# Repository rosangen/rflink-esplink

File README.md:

RFLink-ESPLink pcb
===================

This is a PCB card for use with [RFLink](http://rflink.nl/blog2/) software, [ESP-Link](https://github.com/jeelabs/esp-link), [ESP-Easy](https://github.com/letscontrolit/ESPEasy) or what you find fits you best.
It is mainly for my purpose of getting [IKEA anslut remote control](http://www.ikea.com/se/sv/catalog/products/90300773/) in my Home Assistant setup. And for measure my pellets and power meter.

**You can fill the board so it meat yours need!!**

Use it as a RFLink with receiver and transmitter, and connect to server with USB, add CC2500 module for IKEA asnlut support.

Add a Wemos D1 Mini to get the RFLink more portable and communicate via WiFi via [tcp-mode](https://home-assistant.io/components/rflink/#tcp-mode).
If you just are interested in IKEA anslut, use a CC2500 module + Arduino Pro Mini + Wemos D1 Mini and communicate with MQTT.
 
Inspired by https://github.com/NDBCK/Ansluta-Remote-Controller for Arduino Pro Mini support, and also https://github.com/Genestealer/Home-Assistant-RFLink-Gateway-ESP8266 fore the komplete setup!

Schema
-----------

[Schema pdf](https://github.com/rosangen/rflink-esplink/blob/master/PCB/RfLink-ESPlink.pdf?raw=true "RfLink-ESPlink.pdf")

PCB
------
Size 94 x 96mm

Fore the moment, no PCB is tested, more info to come!

Configurations
-----------
Some configurations explained:

### RFLink USB connected:
```
IC2 Arduino Mega, IC5 Transmitter, IC6 or IC7 Receiver, X1 Antenna connection. 
Option 1: C5,C6 and C7 for better reception with RXB6 receiver.
Option 2: R3, R9, LED1 so se TX communication is visible (receiving data).
```

### RFLink with ESP-link:
```
IC1 ESP, IC2 Arduino Mega, IC5 Transmitter, IC6 or IC7 Receiver. R1, R2, R3.
- Ansluta option: IC4 CC2500, R4-7, C8.
- Option 1 and 2, se above.
```

### Anluta MQTT:
```
IC1 ESP, IC3 Arduino Pro Mini 3.3v, IC4 CC2500 modul, C8.
- Option R9 LED1
```

### EasyESP:
With 1-wire temp and power meter sensor.
```
IC1 ESP, R20-R25 if needed. If lead needed: R10, R11, LED 2, LED3, R20, JP1, R21, JP2. 
Temperatur: DS18B20 connected to JP1
Power meter: LTR4206E ir detector connected to JP2.
```

### Onboard 3.3v converter
If you don't want to use Mega 2560 or ESP interna 3.3v converter you can add U1 (AMS1117 3.3v) and C2, C3, C4.
- PS1 Power selector is for choose input source, IC2 Mega or IC1 ESP 5 volt. (JP5 can only be in used if not Mega 2560 is in use).
- PS2 is the 3.3v source selector, use INT with interna 3.3v converter.

Komponents
-----------

<table>
<tbody>
<tr>
<td><strong>Part</strong></td>
<td><strong>Value</strong></td>
<td><strong>Device/Type</strong></td>
<td><strong>Package/Info</strong></td>
</tr>
<tr>
<td>C1</td>
<td>10&micro;F</td>
<td>CAPACITOR</td>
<td>E2-5</td>
</tr>
<tr>
<td>C2</td>
<td>100nF</td>
<td>CAPACITOR</td>
<td>C0805</td>
</tr>
<tr>
<td>C3</td>
<td>0.1&micro;F</td>
<td>CAPACITOR</td>
<td>E2-5</td>
</tr>
<tr>
<td>C4</td>
<td>10&micro;F</td>
<td>CAPACITOR</td>
<td>E2-5</td>
</tr>
<tr>
<td>C5</td>
<td>100nF</td>
<td>CAPACITOR</td>
<td>C0805</td>
</tr>
<tr>
<td>C6</td>
<td>100nF</td>
<td>CAPACITOR</td>
<td>C0805</td>
</tr>
<tr>
<td>C7</td>
<td>10&micro;F</td>
<td>CPOL-EUE2-5</td>
<td>E2-5</td>
</tr>
<tr>
<td>C8</td>
<td>100nF</td>
<td>CAPACITOR</td>
<td>C0805</td>
</tr>
<tr>
<td>C9</td>
<td>10&micro;F</td>
<td>CPOL-EUE2-5</td>
<td>E2-5</td>
</tr>
<tr>
<td>IC1</td>
<td>WEMOS D1 MINI</td>
<td>WEMOS D1 MINI</td>
<td>&nbsp;WeMos.cc</td>
</tr>
<tr>
<td>IC2</td>
<td>ARDUINO-MEGA</td>
<td>ARDUINO MEGA 2560</td>
</tr>
<tr>
<td>IC3</td>
<td>PRO MINI 3.3V</td>
<td>ARDUINO PRO MINI</td>
</tr>
<tr>
<td>IC4</td>
<td>CC2500</td>
<td>CC2500 MODULE</td>
</tr>
<tr>
<td>IC5</td>
<td>TRANSMITTER 433MHZ</td>
<td>TRANSMITTER 433MHZ</td>
</tr>
<tr>
<td>IC6</td>
<td>RXB6</td>
<td>RECEIVER</td>
</tr>
<tr>
<td>IC7</td>
<td>RTX-MID</td>
<td>RTX-MID</td>
<td>Aurel</td>
</tr>
<tr>
<td>IC8</td>
<td>NRF24L01A</td>
<td>NRF24L01A</td>
<td>NRF24L01</td>
</tr>
<tr>
<td>IC9</td>
<td>ESP-01</td>
<td>ESP8266 Wifi module 01</td>
</tr>
<tr>
<td>J1</td>
<td>JUMPER 2 SMD</td>
<td>Jumper</td>
<td>Aktivate CC2500</td>
</tr>
<tr>
<td>J2</td>
<td>JUMPER 3 SMD</td>
<td>Jumper</td>
<td>3.3 or 5.0V Aurel</td>
</tr>
<tr>
<td>JP1</td>
<td>GS015S-3.81-3P</td>
<td>PCB terminal block</td>
<td>PCB terminal block</td>
</tr>
<tr>
<td>JP2</td>
<td>GS015S-3.81-3P</td>
<td>PCB terminal block</td>
<td>PCB terminal block</td>
</tr>
<tr>
<td>JP3</td>
<td>GS015S-3.81-3P</td>
<td>PCB terminal block</td>
<td>PCB terminal block</td>
</tr>
<tr>
<td>JP4</td>
<td>GS015S-3.81-2P</td>
<td>PCB terminal block</td>
<td>PCB terminal block</td>
</tr>
<tr>
<td>JP5</td>
<td>GS015S-3.81-2P</td>
<td>PCB terminal block</td>
<td>PCB terminal block</td>
</tr>
<tr>
<td>LED1</td>
<td>LED1206</td>
<td>LED-1206</td>
<td>LEDs</td>
</tr>
<tr>
<td>LED2</td>
<td>LED1206</td>
<td>LED-1206</td>
<td>LEDs</td>
</tr>
<tr>
<td>LED3</td>
<td>LED1206</td>
<td>LED-1206</td>
<td>LEDs</td>
</tr>
<tr>
<td>LED4</td>
<td>LED1206</td>
<td>LED-1206</td>
<td>LEDs</td>
</tr>
<tr>
<td>PS1</td>
<td>JUMPER</td>
<td>2 TO 1 POWER</td>
</tr>
<tr>
<td>PS2</td>
<td>JUMPER</td>
<td>3 TO 1 POWER</td>
</tr>
<tr>
<td>R1</td>
<td>470R</td>
<td>RESISTOR R0805</td>
<td>R0805</td>
</tr>
<tr>
<td>R2</td>
<td>470R</td>
<td>RESISTORR0805</td>
<td>R0805</td>
</tr>
<tr>
<td>R3</td>
<td>470R</td>
<td>RESISTORR0805</td>
<td>R0805</td>
</tr>
<tr>
<td>R4</td>
<td>470R</td>
<td>RESISTORR0805</td>
<td>R0805</td>
</tr>
<tr>
<td>R5</td>
<td>470R</td>
<td>RESISTORR0805</td>
<td>R0805</td>
</tr>
<tr>
<td>R6</td>
<td>470R</td>
<td>RESISTORR0805</td>
<td>R0805</td>
</tr>
<tr>
<td>R7</td>
<td>470R</td>
<td>RESISTORR0805</td>
<td>R0805</td>
</tr>
<tr>
<td>R8</td>
<td>1K</td>
<td>RESISTORR0805</td>
<td>R0805</td>
</tr>
<tr>
<td>R9</td>
<td>1K</td>
<td>RESISTORR0805</td>
<td>R0805</td>
</tr>
<tr>
<td>R10</td>
<td>1K</td>
<td>RESISTORR0805</td>
<td>R0805</td>
</tr>
<tr>
<td>R11</td>
<td>1K</td>
<td>RESISTORR0805</td>
<td>R0805</td>
</tr>
<tr>
<td>R12</td>
<td>4k7</td>
<td>RESISTORR0805</td>
<td>R0805</td>
</tr>
<tr>
<td>R13</td>
<td>4k7</td>
<td>RESISTORR0805</td>
<td>R0805</td>
</tr>
<tr>
<td>R20</td>
<td>4k7</td>
<td>RESISTORR0805</td>
<td>R0805</td>
</tr>
<tr>
<td>R21</td>
<td>4k7</td>
<td>RESISTORR0805</td>
<td>R0805</td>
</tr>
<tr>
<td>R22</td>
<td>4k7</td>
<td>RESISTORR0805</td>
<td>R0805</td>
</tr>
<tr>
<td>R23</td>
<td>4k7</td>
<td>RESISTORR0805</td>
<td>R0805</td>
</tr>
<tr>
<td>R24</td>
<td>4k7</td>
<td>RESISTORR0805</td>
<td>R0805</td>
</tr>
<tr>
<td>R25</td>
<td>4k7</td>
<td>RESISTORR0805</td>
<td>R0805</td>
</tr>
<tr>
<td>U1</td>
<td>AMS1117</td>
<td>800mA and 1A Low Dropout (LDO) Positive Regulator</td>
<td>SOT223</td>
</tr>
<tr>
<td>U2</td>
<td>DHT22</td>
<td>DHT-22</td>
</tr>
<tr>
<td>U3</td>
<td>DS18B20</td>
<td>DS18B20</td>
</tr>
<tr>
<td>X1</td>
<td>BU-SMA-V</td>
<td>ANTEN</td>
</tr>
</tbody>
</table>

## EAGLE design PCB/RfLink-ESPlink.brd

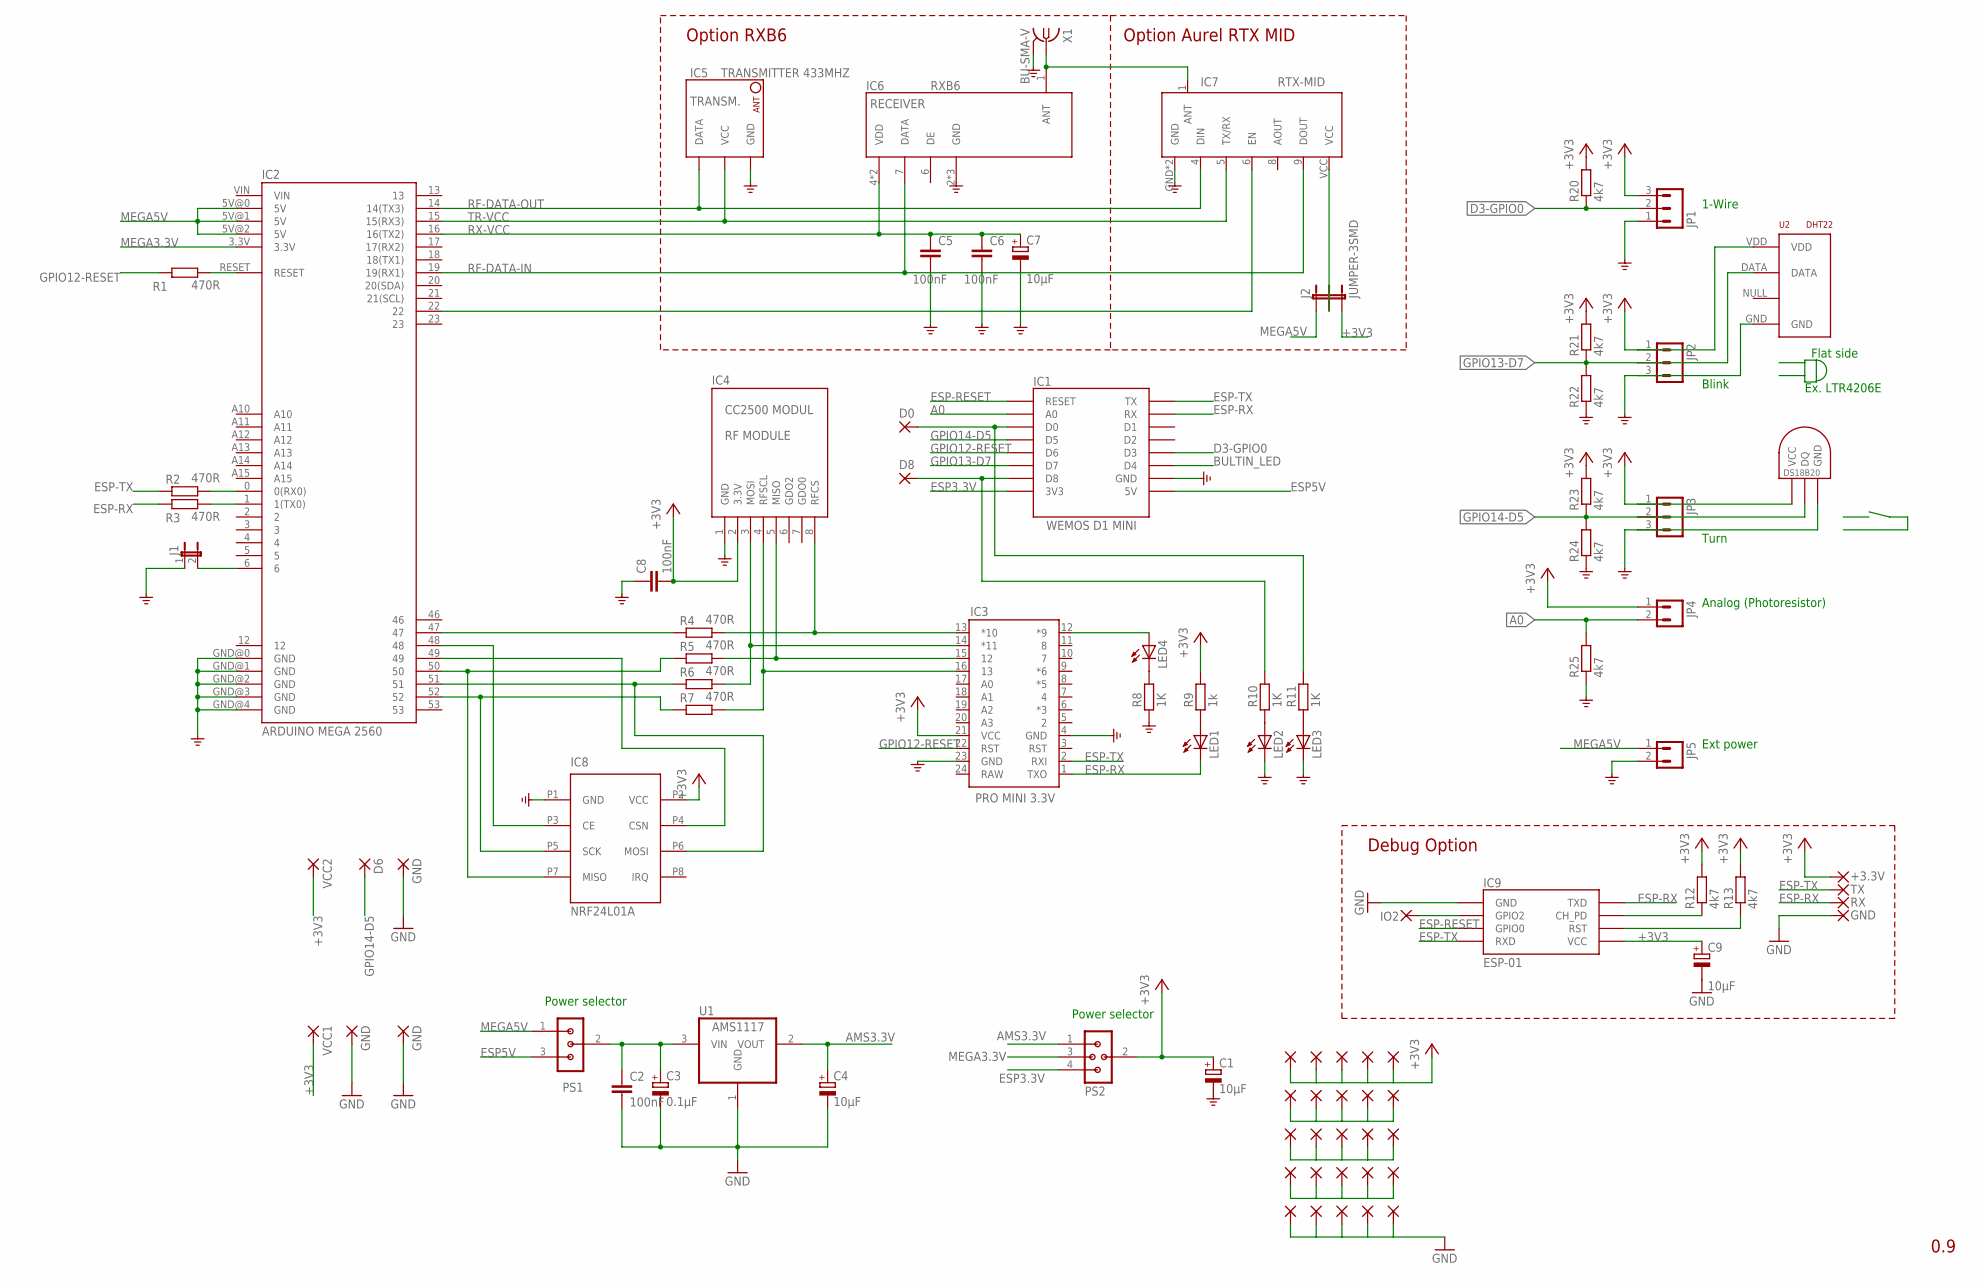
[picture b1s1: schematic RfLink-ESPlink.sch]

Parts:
+3.3V: 1,6/0,9
C1, C4, C7, C9: 10μF; E2-5
C2, C5, C6, C8: 100nF; C0805
C3: 0.1μF; E2-5
D0, D8: 1,6/0,9
D6: D6; 1,6/0,9
G: GND; 1,6/0,9
GND, GND5, GND7: GND; 1,6/0,9
GPIO2: IO2; 1,6/0,9
IC1: WEMOS D1 MINI; WEMOS-D1-MINI
IC2: ARDUINO MEGA 2560; ARDUINO_MEGA_MINI
IC3: PRO MINI 3.3V; ARDUINO_PRO_MINI
IC4: CC2500 MODUL; CC2500
IC5: TRANSMITTER 433MHZ; TRANSMITTER433MHZ
IC6: RXB6; RXB6-LOW-SILKSCREEN
IC7: RTX-MID
IC8: NRF24L01A; NRF24L01
IC9: ESP-01; ESP01
J1: JUMPER-2SMD-NO; SJ_2S-NO
J2: JUMPER-3SMD; SJ_3
JP1, JP2, JP3: GS015S-3.81-3P; GS015S-3.81-3
JP4, JP5: GS015S-3.81-2P; GS015S-3.81-2
LED1, LED2, LED3, LED4: LED1206; LED-1206
P1, P2, P3, P4, P5, P6, P7, P8, P9, P10, P11, P12, P13, P14, P15, P16, P17, P18, P19, P20, P21, P22, P23, P24, P25: 1,6/0,9
PS1: SV2; 2-1
PS2: 3TO1POWER; 3-1
R1, R2, R3, R4, R5, R6, R7: 470R; R0805
R8, R10, R11: 1K; R0805
R9: 1k; R0805
R12, R13, R20, R21, R22, R23, R24, R25: 4k7; R0805
RX: RX; 1,6/0,9
TX: TX; 1,6/0,9
U1: AMS1117; SOT223
U2: DHT22; RHT03_DHT-22
U3: DS18B20; DS1820
VCC1, VCC2: 1,6/0,9
X1: BU-SMA-V

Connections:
+3V3: +3.3V.1, C1.+, C8.2, C9.+, IC3.21 (VCC), IC4.2 (3.3V), IC8.P2 (VCC), IC9.VCC, J2.3, JP1.3, JP2.1, JP3.1, JP4.1, P21.1, P22.1, P23.1, P24.1, P25.1, PS2.2, R9.2, R12.2, R13.2, R20.2, R21.2, R23.2, U2.VDD, U3.VDD (VCC), VCC1.1, VCC2.1
A0: IC1.A0, JP4.2, R25.2
AMS3.3V: C4.+, PS2.1, U1.2 (VOUT)
ANT: IC6.1 (ANT), IC7.1 (ANT), X1.1
BULTIN_LED: IC1.D4
CC250-ACTIV: IC2.6, J1.2
D3-GPIO0: IC1.D3, JP1.2, R20.1
ESP3.3V: IC1.3V3, PS2.4
ESP5V: IC1.5V, PS1.3
ESP-RESET: IC1.RESET, IC9.GPIO0
ESP-RX: IC1.RX, IC3.1 (TXO), IC9.TX (TXD), LED1.C, R3.1, RX.1
ESP-TX: IC1.TX, IC3.2 (RXI), IC9.RX (RXD), R2.2, TX.1
GND: C1.-, C2.2, C3.-, C4.-, C5.1, C6.1, C7.-, C8.1, C9.-, G.1, GND.1, GND5.1, GND7.1, IC1.GND, IC2.GND@0 (GND), IC2.GND@1 (GND), IC2.GND@2 (GND), IC2.GND@3 (GND), IC2.GND@4 (GND), IC3.4 (GND), IC3.23 (GND), IC4.1 (GND), IC5.P$3 (GND), IC6.2 (GND), IC6.3 (GND), IC6.8 (GND), IC7.GND, IC7.GND1 (GND), IC8.P1 (GND), IC9.GND, J1.1, JP1.1, JP2.3, JP3.3, JP5.2, LED2.C, LED3.C, P11.1, P12.1, P13.1, P14.1, P15.1, R8.1, R22.1, R24.1, R25.1, U1.1 (GND), U2.GND, U3.GND, X1.2, X1.3 (2), X1.4 (2), X1.5 (2)
GPIO12-RESET: IC1.D6, IC3.22 (RST), R1.2
GPIO13-D7: IC1.D7, JP2.2, R21.1, R22.2, U2.DATA
GPIO14-D5: D6.1, IC1.D5, JP3.2, R23.1, R24.2, U3.DQ
MEGA3.3V: IC2.3.3V, PS2.3
MEGA5V: IC2.5V@0 (5V), IC2.5V@1 (5V), IC2.5V@2 (5V), J2.1, JP5.1, PS1.1
MEGA-RX: IC2.0 (0(RX0)), R2.1
MEGA-TX: IC2.1 (1(TX0)), R3.2
unnamed: IC2.47, R4.1
unnamed: IC2.50, IC8.P7 (MISO), R5.1
unnamed: IC2.51, IC8.P6 (MOSI), R6.1
unnamed: IC2.52, IC8.P5 (SCK), R7.1
unnamed: LED3.A, R11.1
unnamed: D8.1, IC1.D8, R10.2
unnamed: IC3.14 (*11), IC4.3 (MOSI), R6.2
unnamed: IC2.22, IC7.6 (EN)
unnamed: IC3.16 (13), IC4.4 (RFSCL), R7.2
unnamed: IC3.15 (12), IC4.5 (MISO), R5.2
unnamed: IC3.13 (*10), IC4.8 (RFCS), R4.2
unnamed: IC2.48, IC8.P3 (CE)
unnamed: IC2.49, IC8.P4 (CSN)
unnamed: LED1.A, R9.1
unnamed: LED2.A, R10.1
unnamed: LED4.C, R8.2
unnamed: D0.1, IC1.D0, R11.2
unnamed: IC3.12 (*9), LED4.A
unnamed: C2.1, C3.+, PS1.2, U1.3 (VIN)
unnamed: IC9.CH_PD, R12.1
unnamed: IC7.VCC, J2.2
unnamed: IC9.RST, R13.1
unnamed: GPIO2.1, IC9.GPIO2
unnamed: P1.1, P2.1, P3.1, P4.1, P5.1
unnamed: P6.1, P7.1, P8.1, P9.1, P10.1
unnamed: P16.1, P17.1, P18.1, P19.1, P20.1
RESET: IC2.RESET, R1.1
RF-DATA-IN: IC2.19 (19(RX1)), IC6.7 (DATA), IC7.9 (DOUT)
RF-DATA-OUT: IC2.14 (14(TX3)), IC5.P$1 (DATA), IC7.4 (DIN)
RX-VCC: C5.2, C6.2, C7.+, IC2.16 (16(TX2)), IC6.4 (VDD), IC6.5 (VDD)
TR-VCC: IC2.15 (15(RX3)), IC5.P$2 (VCC), IC7.5 (TX/RX)

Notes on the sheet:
Power selector
Blink
Flat side
Ex. LTR4206E
Analog (Photoresistor)
Turn
1-Wire
Option RXB6
Option Aurel RTX MID
Ext power
0.9
Debug Option

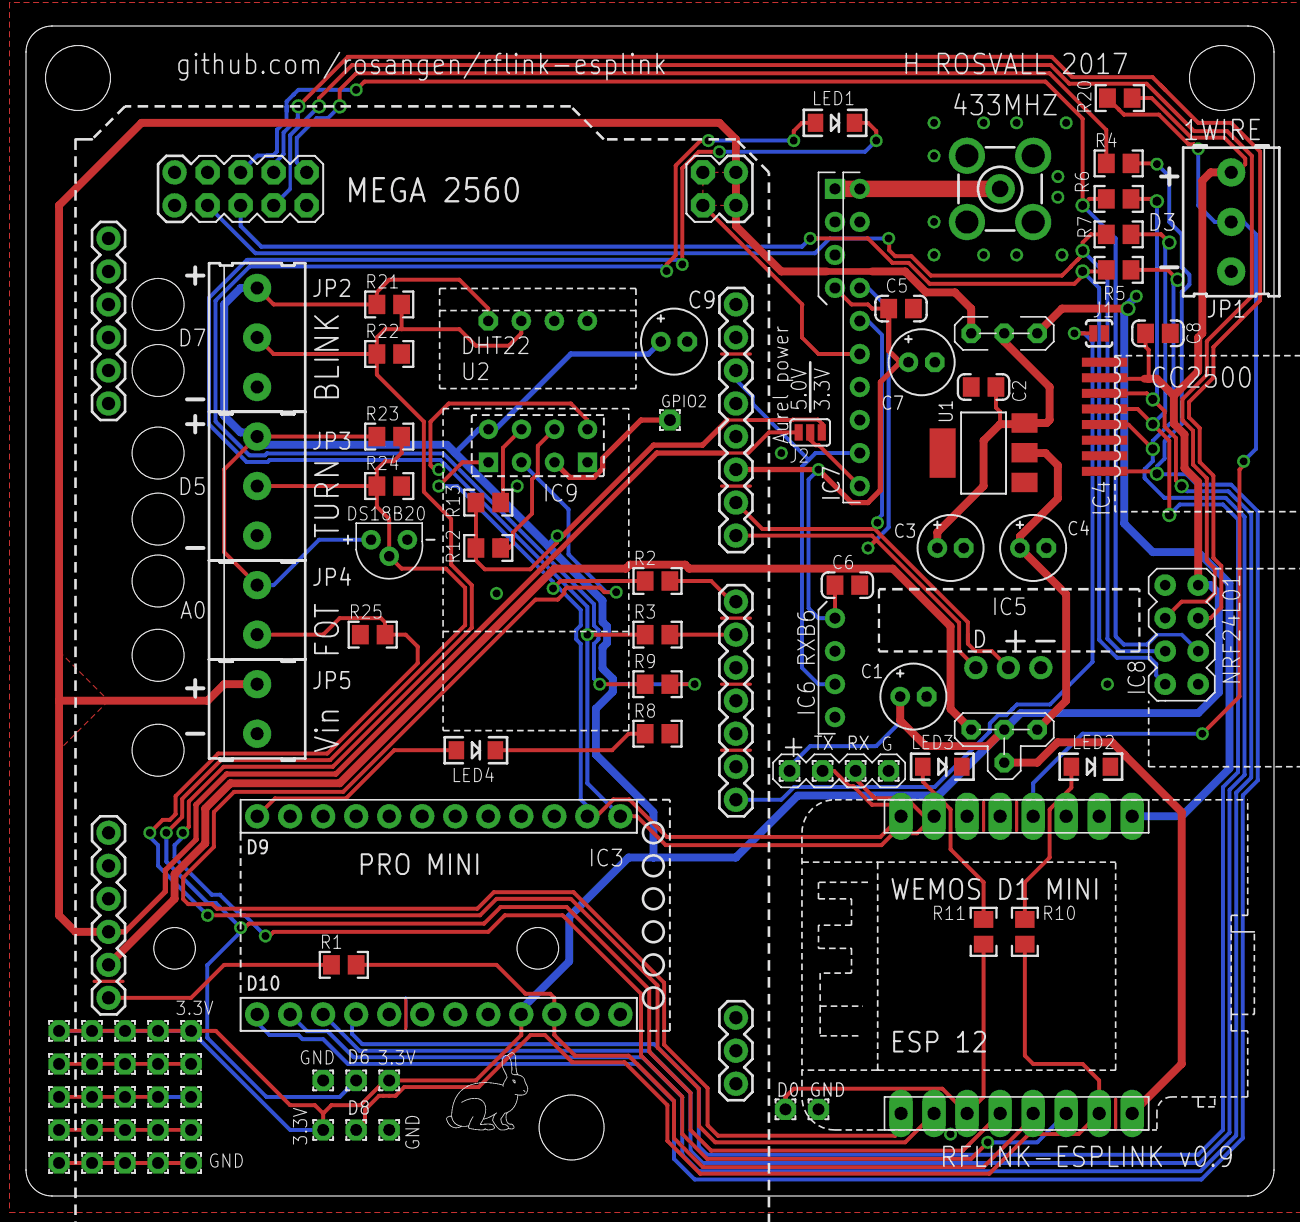
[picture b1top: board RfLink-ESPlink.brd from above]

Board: 2 copper layers, 96.0 x 90.0 mm, 93 parts (0 on the bottom side), 50 nets.

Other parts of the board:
U$28: RABBIT-SILK

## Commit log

2017-10-03 Update Schema
    Moved R5 closer to Mega 2560
2017-10-03 Readme add
2017-10-03 More information
2017-10-06 New pcb revison 0.81
    Added resistors to all Arduino Mega 2560 pins connected to ESP, value
    470R. Added JP5 for external power supplt if Mega not are in use.
    Unnecessary pins removed from Mega 2560.
2017-10-06 Komponents miss update
2017-10-23 New pcb revison 0.9
    Added ESP-01 for easy serial debug of Wemos ESP. This is the
    manufactured version. And some other good to have functions!
2017-10-23 Removing old files
2017-10-23 adds GNU General Public License v3.0
2017-10-23 Different configuration scenarios
2017-10-23 Adds pdf link

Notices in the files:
parts and their libraries:
SparkFun: Licensing: CC v3.0 Share-Alike You are welcome to use this library for commercial purposes.
